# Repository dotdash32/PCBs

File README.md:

# PCBs

Printed Circuit Board Designs, primarily for keyboards.

I'm keeping all the PCB files here, including works in progress and ones that aren't labelled super well.  
Not everything is tested, but everything should be mostly ok.

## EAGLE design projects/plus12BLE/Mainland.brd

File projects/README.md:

# Projects

All my projects in EAGLE, even some outdated/inactive ones.

## Active Projects

* plus12 (upcoming GB as of summer 2018)

* Handwire Support

Other projects are outdated/inactive.  I'm keeping these here in case anyone wants a CamelDox.

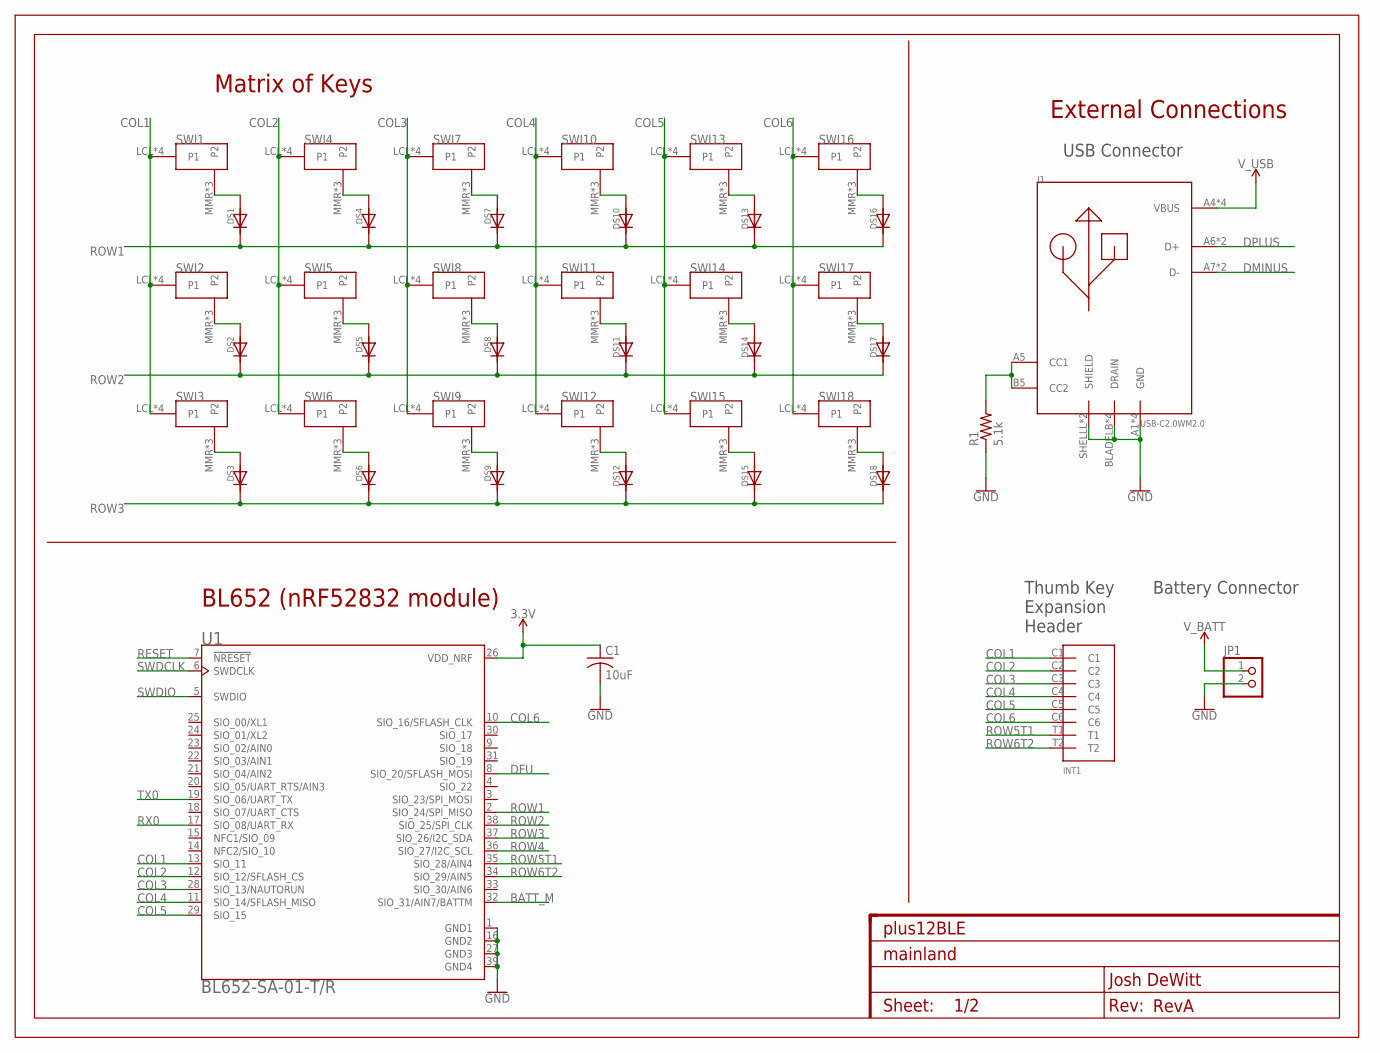
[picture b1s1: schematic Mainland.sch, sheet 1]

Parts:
C1: 10uF; C0805K
DS1, DS2, DS3, DS4, DS5, DS6, DS7, DS8, DS9, DS10, DS11, DS12, DS13, DS14, DS15, DS16, DS17, DS18: DIODECOMBO; DIODE_COMBO
FRAME1: FRAME_LTR_CU_MARK; FR-LTR-ON-PCB
INT1: INTRCNNT4X2; INTRRIBBON
J1: USB-C2.0WM2.0; WM17904_SIMP
JP1: PINHD-1X2; 1X02
R1: 5.1k; R0603
SWI1, SWI2, SWI3, SWI4, SWI5, SWI6, SWI7, SWI8, SWI9, SWI10, SWI11, SWI12, SWI13, SWI14, SWI15, SWI16, SWI17, SWI18: MX/ALPSDOUBLE_SLOT; DOUBLED_SLOTS
U1: BL652-SA-01-T/R; XCVR_BL652-SA-01-T/R

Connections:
3.3V: C1.1, U1.26 (VDD_NRF); also elsewhere on the board
BATT_M: U1.32 (SIO_31/AIN7/BATTM); also elsewhere on the board
COL1: INT1.C1, SWI1.LCL (P1), SWI1.LLP (P1), SWI1.LRLP (P1), SWI1.MML (P1), SWI2.LCL (P1), SWI2.LLP (P1), SWI2.LRLP (P1), SWI2.MML (P1), SWI3.LCL (P1), SWI3.LLP (P1), SWI3.LRLP (P1), SWI3.MML (P1), U1.13 (SIO_11)
COL2: INT1.C2, SWI4.LCL (P1), SWI4.LLP (P1), SWI4.LRLP (P1), SWI4.MML (P1), SWI5.LCL (P1), SWI5.LLP (P1), SWI5.LRLP (P1), SWI5.MML (P1), SWI6.LCL (P1), SWI6.LLP (P1), SWI6.LRLP (P1), SWI6.MML (P1), U1.12 (SIO_12/SFLASH_CS)
COL3: INT1.C3, SWI7.LCL (P1), SWI7.LLP (P1), SWI7.LRLP (P1), SWI7.MML (P1), SWI8.LCL (P1), SWI8.LLP (P1), SWI8.LRLP (P1), SWI8.MML (P1), SWI9.LCL (P1), SWI9.LLP (P1), SWI9.LRLP (P1), SWI9.MML (P1), U1.28 (SIO_13/NAUTORUN)
COL4: INT1.C4, SWI10.LCL (P1), SWI10.LLP (P1), SWI10.LRLP (P1), SWI10.MML (P1), SWI11.LCL (P1), SWI11.LLP (P1), SWI11.LRLP (P1), SWI11.MML (P1), SWI12.LCL (P1), SWI12.LLP (P1), SWI12.LRLP (P1), SWI12.MML (P1), U1.11 (SIO_14/SFLASH_MISO)
COL5: INT1.C5, SWI13.LCL (P1), SWI13.LLP (P1), SWI13.LRLP (P1), SWI13.MML (P1), SWI14.LCL (P1), SWI14.LLP (P1), SWI14.LRLP (P1), SWI14.MML (P1), SWI15.LCL (P1), SWI15.LLP (P1), SWI15.LRLP (P1), SWI15.MML (P1), U1.29 (SIO_15)
COL6: INT1.C6, SWI16.LCL (P1), SWI16.LLP (P1), SWI16.LRLP (P1), SWI16.MML (P1), SWI17.LCL (P1), SWI17.LLP (P1), SWI17.LRLP (P1), SWI17.MML (P1), SWI18.LCL (P1), SWI18.LLP (P1), SWI18.LRLP (P1), SWI18.MML (P1), U1.10 (SIO_16/SFLASH_CLK)
DFU: U1.8 (SIO_20/SFLASH_MOSI); also elsewhere on the board
DMINUS: J1.A7 (D-), J1.B7 (D-); also elsewhere on the board
DPLUS: J1.A6 (D+), J1.B6 (D+); also elsewhere on the board
GND: C1.2, J1.A1 (GND), J1.A12 (GND), J1.B1 (GND), J1.B12 (GND), J1.BLADELB (DRAIN), J1.BLADELF (DRAIN), J1.BLADERB (DRAIN), J1.BLADERF (DRAIN), J1.SHELLL (SHIELD), J1.SHELLR (SHIELD), JP1.2, R1.1, U1.1 (GND1), U1.16 (GND2), U1.27 (GND3), U1.39 (GND4); also elsewhere on the board
unnamed: DS1.ANOST (AN), DS1.ANOT (AN), SWI1.MMR (P2), SWI1.RCL (P2), SWI1.RLMID (P2)
unnamed: DS4.ANOST (AN), DS4.ANOT (AN), SWI4.MMR (P2), SWI4.RCL (P2), SWI4.RLMID (P2)
unnamed: DS7.ANOST (AN), DS7.ANOT (AN), SWI7.MMR (P2), SWI7.RCL (P2), SWI7.RLMID (P2)
unnamed: DS10.ANOST (AN), DS10.ANOT (AN), SWI10.MMR (P2), SWI10.RCL (P2), SWI10.RLMID (P2)
unnamed: DS13.ANOST (AN), DS13.ANOT (AN), SWI13.MMR (P2), SWI13.RCL (P2), SWI13.RLMID (P2)
unnamed: DS16.ANOST (AN), DS16.ANOT (AN), SWI16.MMR (P2), SWI16.RCL (P2), SWI16.RLMID (P2)
unnamed: DS2.ANOST (AN), DS2.ANOT (AN), SWI2.MMR (P2), SWI2.RCL (P2), SWI2.RLMID (P2)
unnamed: DS5.ANOST (AN), DS5.ANOT (AN), SWI5.MMR (P2), SWI5.RCL (P2), SWI5.RLMID (P2)
unnamed: DS8.ANOST (AN), DS8.ANOT (AN), SWI8.MMR (P2), SWI8.RCL (P2), SWI8.RLMID (P2)
unnamed: DS11.ANOST (AN), DS11.ANOT (AN), SWI11.MMR (P2), SWI11.RCL (P2), SWI11.RLMID (P2)
unnamed: DS14.ANOST (AN), DS14.ANOT (AN), SWI14.MMR (P2), SWI14.RCL (P2), SWI14.RLMID (P2)
unnamed: DS17.ANOST (AN), DS17.ANOT (AN), SWI17.MMR (P2), SWI17.RCL (P2), SWI17.RLMID (P2)
unnamed: DS3.ANOST (AN), DS3.ANOT (AN), SWI3.MMR (P2), SWI3.RCL (P2), SWI3.RLMID (P2)
unnamed: DS6.ANOST (AN), DS6.ANOT (AN), SWI6.MMR (P2), SWI6.RCL (P2), SWI6.RLMID (P2)
unnamed: DS9.ANOST (AN), DS9.ANOT (AN), SWI9.MMR (P2), SWI9.RCL (P2), SWI9.RLMID (P2)
unnamed: DS12.ANOST (AN), DS12.ANOT (AN), SWI12.MMR (P2), SWI12.RCL (P2), SWI12.RLMID (P2)
unnamed: DS15.ANOST (AN), DS15.ANOT (AN), SWI15.MMR (P2), SWI15.RCL (P2), SWI15.RLMID (P2)
unnamed: DS18.ANOST (AN), DS18.ANOT (AN), SWI18.MMR (P2), SWI18.RCL (P2), SWI18.RLMID (P2)
unnamed: J1.A5 (CC1), J1.B5 (CC2), R1.2
RESET: U1.7 (!NRESET); also elsewhere on the board
ROW1: DS1.CATST (CAT), DS1.CATT (CAT), DS4.CATST (CAT), DS4.CATT (CAT), DS7.CATST (CAT), DS7.CATT (CAT), DS10.CATST (CAT), DS10.CATT (CAT), DS13.CATST (CAT), DS13.CATT (CAT), DS16.CATST (CAT), DS16.CATT (CAT), U1.2 (SIO_24/SPI_MISO)
ROW2: DS2.CATST (CAT), DS2.CATT (CAT), DS5.CATST (CAT), DS5.CATT (CAT), DS8.CATST (CAT), DS8.CATT (CAT), DS11.CATST (CAT), DS11.CATT (CAT), DS14.CATST (CAT), DS14.CATT (CAT), DS17.CATST (CAT), DS17.CATT (CAT), U1.38 (SIO_25/SPI_CLK)
ROW3: DS3.CATST (CAT), DS3.CATT (CAT), DS6.CATST (CAT), DS6.CATT (CAT), DS9.CATST (CAT), DS9.CATT (CAT), DS12.CATST (CAT), DS12.CATT (CAT), DS15.CATST (CAT), DS15.CATT (CAT), DS18.CATST (CAT), DS18.CATT (CAT), U1.37 (SIO_26/I2C_SDA)
ROW4: U1.36 (SIO_27/I2C_SCL)
ROW5T1: INT1.T1, U1.35 (SIO_28/AIN4)
ROW6T2: INT1.T2, U1.34 (SIO_29/AIN5)
RX0: U1.17 (SIO_08/UART_RX); also elsewhere on the board
SWDCLK: U1.6 (SWDCLK); also elsewhere on the board
SWDIO: U1.5 (SWDIO); also elsewhere on the board
TX0: U1.19 (SIO_06/UART_TX); also elsewhere on the board
V_BATT: JP1.1; also elsewhere on the board
V_USB: J1.A4 (VBUS), J1.A9 (VBUS), J1.B4 (VBUS), J1.B9 (VBUS); also elsewhere on the board

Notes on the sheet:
Matrix of Keys
External Connections
USB Connector
Battery Connector
Thumb Key Expansion Header
BL652 (nRF52832 module)

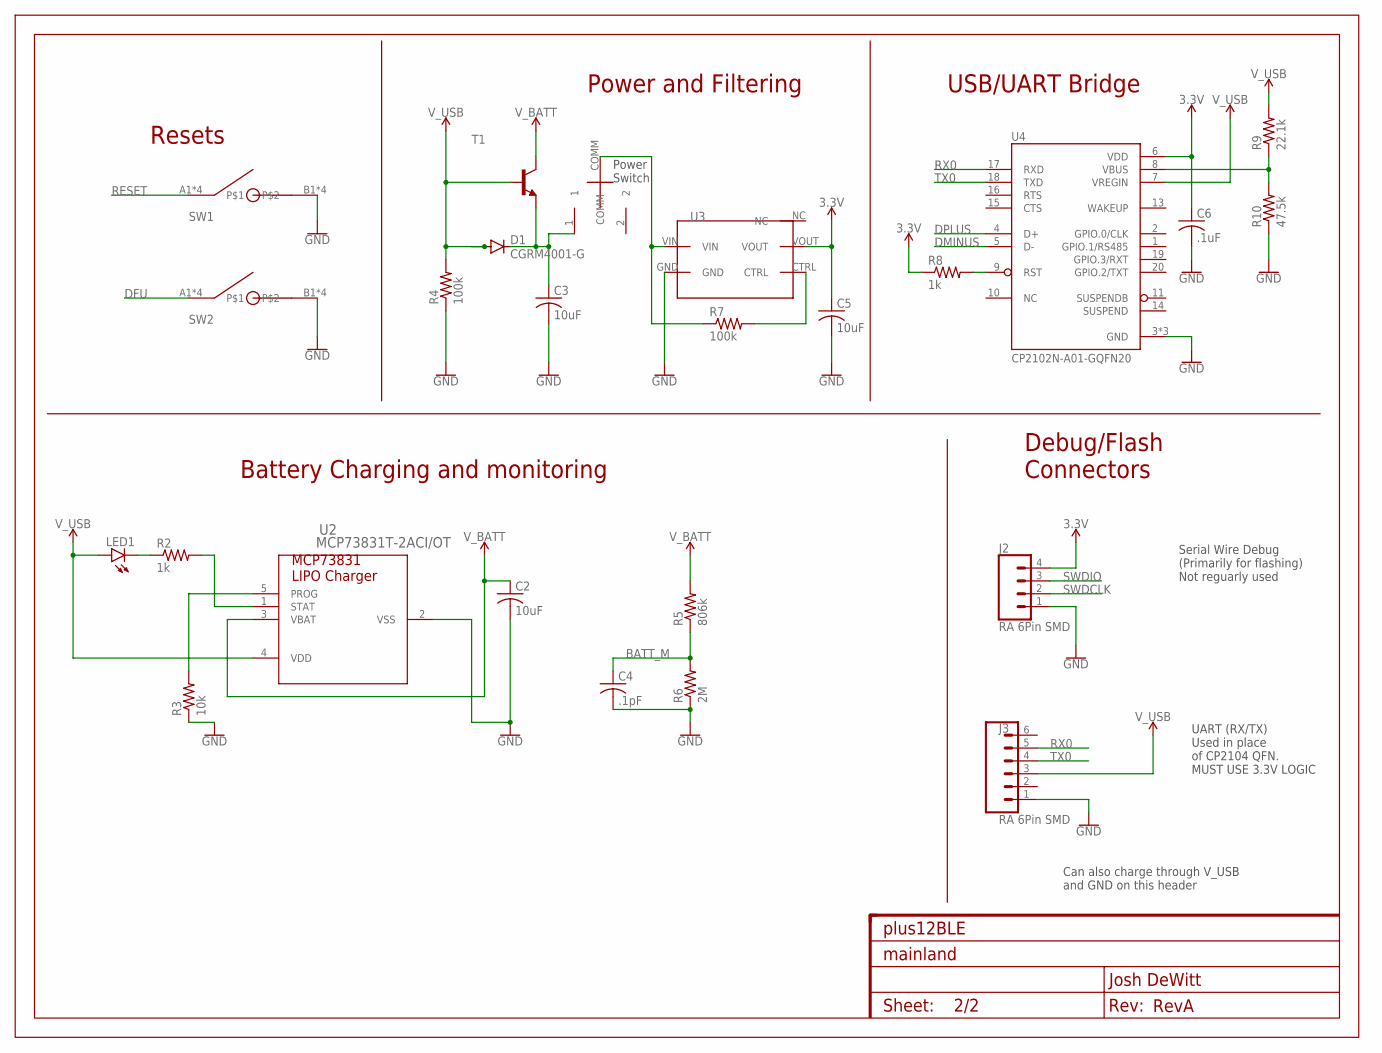
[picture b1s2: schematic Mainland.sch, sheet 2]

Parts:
C2, C3, C5: 10uF; C0805K
C4: .1pF; C0603
C6: .1uF; C0603
D1: CGRM4001-G; SOD-123_MINI-SMA
FRAME2: FRAME_LTR_CU_MARK; FR-LTR-ON-PCB
J2: RA 6Pin SMD; 1X04_SMD_RA_FEMALE
J3: RA 6Pin SMD; 1X06-SMD_RA_MALE
LED1: LEDCHIP-LED0603; CHIP-LED0603
R2, R8: 1k; R0603
R3: 10k; R0603
R4, R7: 100k; R0603
R5: 806k; R0603
R6: 2M; R0603
R9: 22.1k; R0603
R10: 47.5k; R0603
SW1, SW2: RSTSWSMALL_SMD; EVP-BBA
SW3: SLIDER_SWITCH; MHSS1105
T1: BC808-NPN-SOT23-BEC; SOT23-BEC
U2: MCP73831T-2ACI/OT; SOT-23-5_MC
U3: TCR2EF
U4: CP2102N-A01-GQFN20; SILABS_QFN20

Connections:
3.3V: C5.1, C6.1, J2.4, R8.1, U3.VOUT, U4.6 (VDD); also elsewhere on the board
BATT_M: C4.1, R5.1, R6.2; also elsewhere on the board
DFU: SW2.A1, SW2.A2, SW2.A3, SW2.A4; also elsewhere on the board
DMINUS: U4.5 (D-); also elsewhere on the board
DPLUS: U4.4 (D+); also elsewhere on the board
GND: C2.2, C3.2, C4.2, C5.2, C6.2, J2.1, J3.1, R3.1, R4.1, R6.1, R10.1, SW1.B1, SW1.B2, SW1.B3, SW1.B4, SW2.B1, SW2.B2, SW2.B3, SW2.B4, U2.2 (VSS), U3.GND, U4.3 (GND), U4.12 (GND), U4.21 (GND); also elsewhere on the board
unnamed: R7.2, U3.CTRL
unnamed: R7.1, SW3.COMM, U3.VIN
unnamed: LED1.C, R2.1
unnamed: R2.2, U2.1 (STAT)
unnamed: R3.2, U2.5 (PROG)
unnamed: R9.1, R10.2, U4.8 (VBUS)
unnamed: R8.2, U4.9 (RST)
unnamed: C3.1, D1.C, SW3.1, T1.E
RESET: SW1.A1, SW1.A2, SW1.A3, SW1.A4; also elsewhere on the board
RX0: J3.5, U4.17 (RXD); also elsewhere on the board
SWDCLK: J2.2; also elsewhere on the board
SWDIO: J2.3; also elsewhere on the board
TX0: J3.4, U4.18 (TXD); also elsewhere on the board
V_BATT: C2.1, R5.2, T1.C, U2.3 (VBAT); also elsewhere on the board
V_USB: D1.A, J3.3, LED1.A, R4.2, R9.2, T1.B, U2.4 (VDD), U4.7 (VREGIN); also elsewhere on the board

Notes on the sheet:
Resets
Power and Filtering
Battery Charging and monitoring
USB/UART Bridge
Debug/Flash Connectors
Serial Wire Debug (Primarily for flashing) Not reguarly used
UART (RX/TX) Used in place of CP2104 QFN. MUST USE 3.3V LOGIC
Can also charge through V_USB and GND on this header
Power Switch

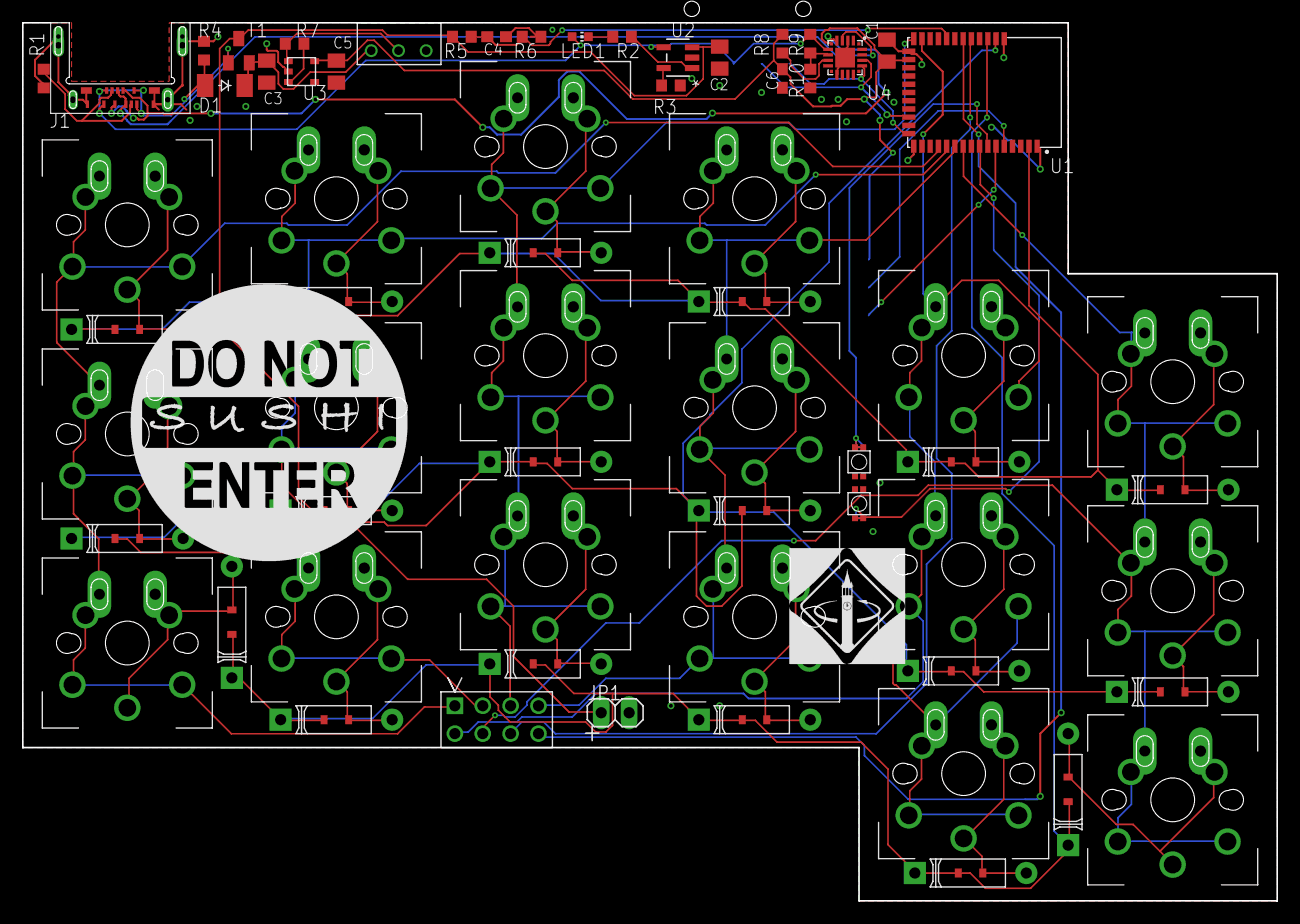
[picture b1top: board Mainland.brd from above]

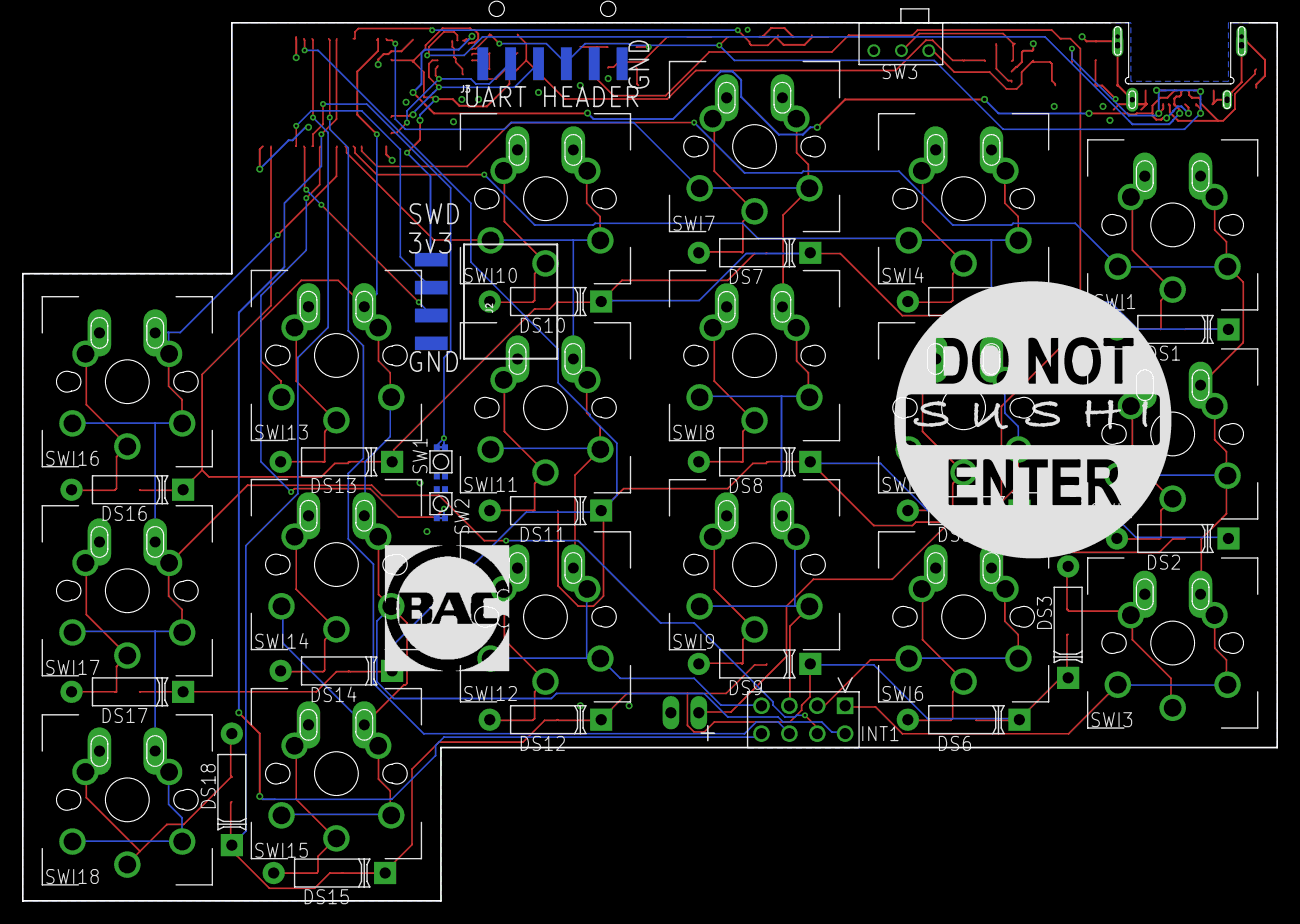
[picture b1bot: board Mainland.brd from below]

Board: 2 copper layers, 114.3 x 80.0 mm, 73 parts (4 on the bottom side), 51 nets.

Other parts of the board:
U$1, U$3: 1INCH_TOP
U$2: BAC_SELLOUT
U$4: IEEE_BERKELEY

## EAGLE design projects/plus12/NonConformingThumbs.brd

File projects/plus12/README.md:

# Plus 12

A split keyboard with a bunch of different options.
There are 2 basic main matrix options, either 5 or 6 columns.
There are 3 main thumb configurations:
a full circuluar curve, adjustable down to 3 keys,
a circular curve into a straight row at key four, adjustable down to 5 keys (4 and fewer is the same as the full circle),
a straight row of keys, adjustable down to 3 keys.
There is potential for a 4x2 grid (like a Mitosis board) in the works as well.

[Current Geekhack](https://geekhack.org/index.php?topic=96658.0) and [Reddit](https://www.reddit.com/r/MechanicalKeyboards/comments/8zpj9u/ic_plus12_split_ergonomic_keyboard/) interest check threads.

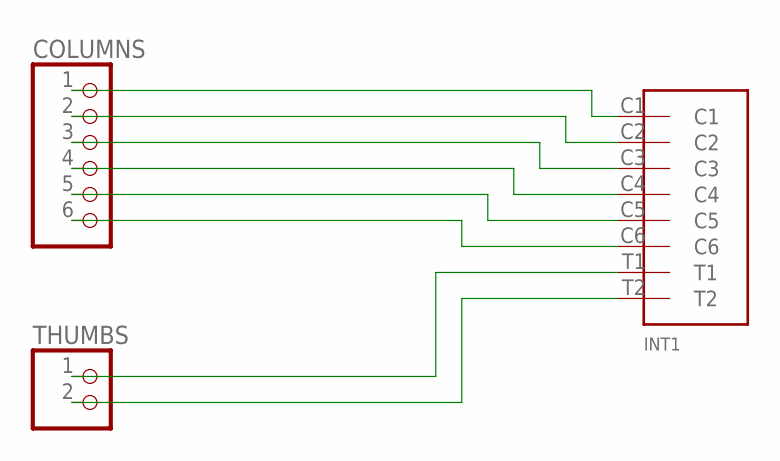
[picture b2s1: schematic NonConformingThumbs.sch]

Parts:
COLUMNS: PINHD-1X6; 1X06
INT1: INTRCNNT4X2; INTRRIBBON
THUMBS: PINHD-1X2; 1X02

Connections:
unnamed: COLUMNS.1, INT1.C1
unnamed: COLUMNS.2, INT1.C2
unnamed: COLUMNS.3, INT1.C3
unnamed: COLUMNS.4, INT1.C4
unnamed: COLUMNS.5, INT1.C5
unnamed: COLUMNS.6, INT1.C6
unnamed: INT1.T1, THUMBS.1
unnamed: INT1.T2, THUMBS.2

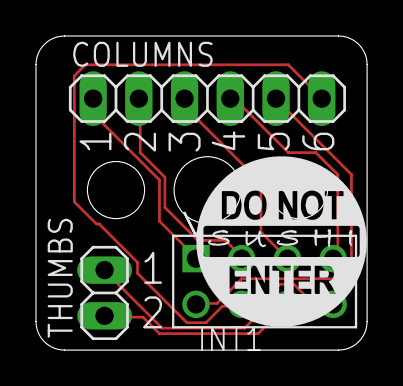
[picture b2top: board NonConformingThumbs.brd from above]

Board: 2 copper layers, 18.4 x 17.4 mm, 4 parts (0 on the bottom side), 8 nets.

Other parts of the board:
U$1: 3_8INCH_TOP

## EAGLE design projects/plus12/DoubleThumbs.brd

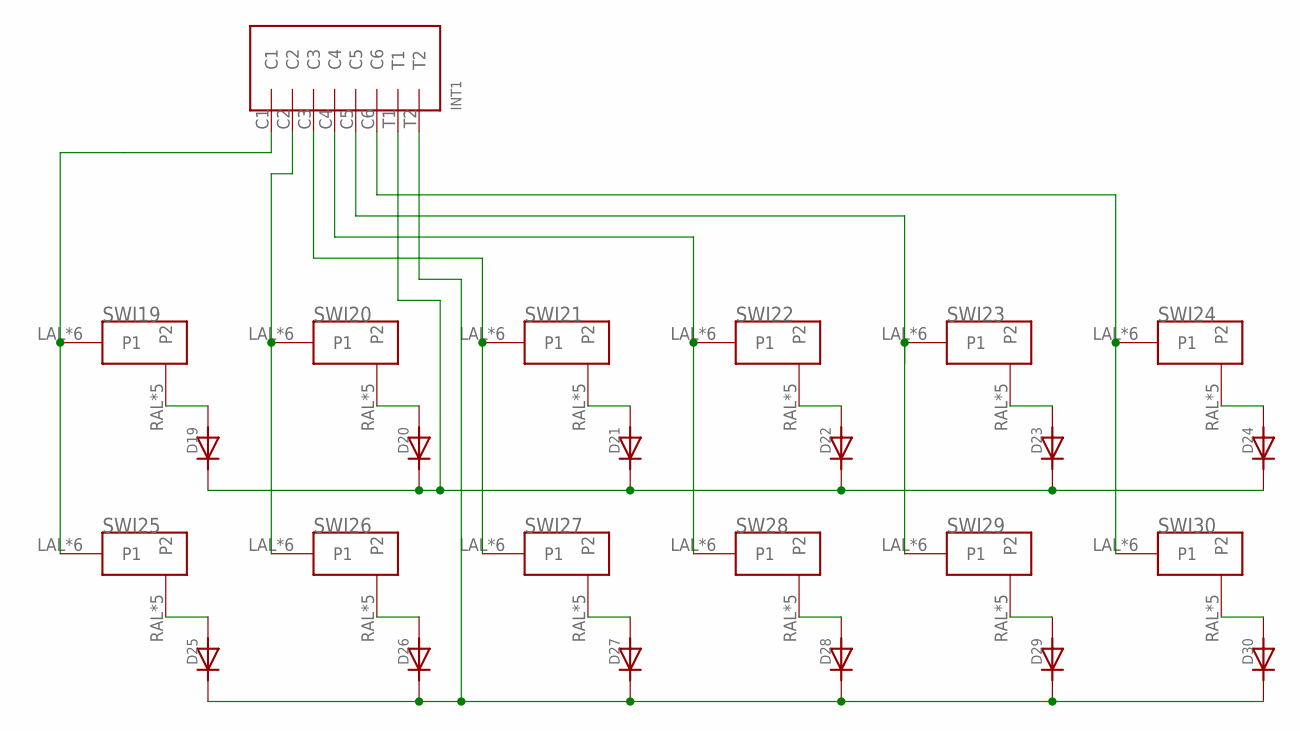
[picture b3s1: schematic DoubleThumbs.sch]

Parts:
D19, D20, D21, D22, D23, D24, D25, D26, D27, D28, D29, D30: DIODE; DIODE_COMBO
INT1: INTRCNNT4X2; INTRRIBBON
SW28: MX/ALPSDOUBLESIDED; DOUBLED_MX/ALPS
SWI19, SWI20, SWI21, SWI22, SWI23, SWI24, SWI25, SWI26, SWI27, SWI29, SWI30: MX/ALPSDOUBLESIDED; DOUBLED_MX/ALPS

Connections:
unnamed: D19.ANOSB (AN), D19.ANOST (AN), D19.ANOT (AN), SWI19.RAL (P2), SWI19.RAR (P2), SWI19.RCL (P2), SWI19.RCR (P2), SWI19.RLMID (P2)
unnamed: D20.ANOSB (AN), D20.ANOST (AN), D20.ANOT (AN), SWI20.RAL (P2), SWI20.RAR (P2), SWI20.RCL (P2), SWI20.RCR (P2), SWI20.RLMID (P2)
unnamed: D21.ANOSB (AN), D21.ANOST (AN), D21.ANOT (AN), SWI21.RAL (P2), SWI21.RAR (P2), SWI21.RCL (P2), SWI21.RCR (P2), SWI21.RLMID (P2)
unnamed: D22.ANOSB (AN), D22.ANOST (AN), D22.ANOT (AN), SWI22.RAL (P2), SWI22.RAR (P2), SWI22.RCL (P2), SWI22.RCR (P2), SWI22.RLMID (P2)
unnamed: D23.ANOSB (AN), D23.ANOST (AN), D23.ANOT (AN), SWI23.RAL (P2), SWI23.RAR (P2), SWI23.RCL (P2), SWI23.RCR (P2), SWI23.RLMID (P2)
unnamed: D24.ANOSB (AN), D24.ANOST (AN), D24.ANOT (AN), SWI24.RAL (P2), SWI24.RAR (P2), SWI24.RCL (P2), SWI24.RCR (P2), SWI24.RLMID (P2)
unnamed: D25.ANOSB (AN), D25.ANOST (AN), D25.ANOT (AN), SWI25.RAL (P2), SWI25.RAR (P2), SWI25.RCL (P2), SWI25.RCR (P2), SWI25.RLMID (P2)
unnamed: D26.ANOSB (AN), D26.ANOST (AN), D26.ANOT (AN), SWI26.RAL (P2), SWI26.RAR (P2), SWI26.RCL (P2), SWI26.RCR (P2), SWI26.RLMID (P2)
unnamed: D27.ANOSB (AN), D27.ANOST (AN), D27.ANOT (AN), SWI27.RAL (P2), SWI27.RAR (P2), SWI27.RCL (P2), SWI27.RCR (P2), SWI27.RLMID (P2)
unnamed: D28.ANOSB (AN), D28.ANOST (AN), D28.ANOT (AN), SW28.RAL (P2), SW28.RAR (P2), SW28.RCL (P2), SW28.RCR (P2), SW28.RLMID (P2)
unnamed: D29.ANOSB (AN), D29.ANOST (AN), D29.ANOT (AN), SWI29.RAL (P2), SWI29.RAR (P2), SWI29.RCL (P2), SWI29.RCR (P2), SWI29.RLMID (P2)
unnamed: D30.ANOSB (AN), D30.ANOST (AN), D30.ANOT (AN), SWI30.RAL (P2), SWI30.RAR (P2), SWI30.RCL (P2), SWI30.RCR (P2), SWI30.RLMID (P2)
unnamed: D25.CATSB (CAT), D25.CATST (CAT), D25.CATT (CAT), D26.CATSB (CAT), D26.CATST (CAT), D26.CATT (CAT), D27.CATSB (CAT), D27.CATST (CAT), D27.CATT (CAT), D28.CATSB (CAT), D28.CATST (CAT), D28.CATT (CAT), D29.CATSB (CAT), D29.CATST (CAT), D29.CATT (CAT), D30.CATSB (CAT), D30.CATST (CAT), D30.CATT (CAT), INT1.T2
unnamed: INT1.C1, SWI19.LAL (P1), SWI19.LAR (P1), SWI19.LCL (P1), SWI19.LCR (P1), SWI19.LLP (P1), SWI19.LRLP (P1), SWI25.LAL (P1), SWI25.LAR (P1), SWI25.LCL (P1), SWI25.LCR (P1), SWI25.LLP (P1), SWI25.LRLP (P1)
unnamed: INT1.C2, SWI20.LAL (P1), SWI20.LAR (P1), SWI20.LCL (P1), SWI20.LCR (P1), SWI20.LLP (P1), SWI20.LRLP (P1), SWI26.LAL (P1), SWI26.LAR (P1), SWI26.LCL (P1), SWI26.LCR (P1), SWI26.LLP (P1), SWI26.LRLP (P1)
unnamed: INT1.C3, SWI21.LAL (P1), SWI21.LAR (P1), SWI21.LCL (P1), SWI21.LCR (P1), SWI21.LLP (P1), SWI21.LRLP (P1), SWI27.LAL (P1), SWI27.LAR (P1), SWI27.LCL (P1), SWI27.LCR (P1), SWI27.LLP (P1), SWI27.LRLP (P1)
unnamed: INT1.C4, SW28.LAL (P1), SW28.LAR (P1), SW28.LCL (P1), SW28.LCR (P1), SW28.LLP (P1), SW28.LRLP (P1), SWI22.LAL (P1), SWI22.LAR (P1), SWI22.LCL (P1), SWI22.LCR (P1), SWI22.LLP (P1), SWI22.LRLP (P1)
unnamed: INT1.C5, SWI23.LAL (P1), SWI23.LAR (P1), SWI23.LCL (P1), SWI23.LCR (P1), SWI23.LLP (P1), SWI23.LRLP (P1), SWI29.LAL (P1), SWI29.LAR (P1), SWI29.LCL (P1), SWI29.LCR (P1), SWI29.LLP (P1), SWI29.LRLP (P1)
unnamed: INT1.C6, SWI24.LAL (P1), SWI24.LAR (P1), SWI24.LCL (P1), SWI24.LCR (P1), SWI24.LLP (P1), SWI24.LRLP (P1), SWI30.LAL (P1), SWI30.LAR (P1), SWI30.LCL (P1), SWI30.LCR (P1), SWI30.LLP (P1), SWI30.LRLP (P1)
unnamed: D19.CATSB (CAT), D19.CATST (CAT), D19.CATT (CAT), D20.CATSB (CAT), D20.CATST (CAT), D20.CATT (CAT), D21.CATSB (CAT), D21.CATST (CAT), D21.CATT (CAT), D22.CATSB (CAT), D22.CATST (CAT), D22.CATT (CAT), D23.CATSB (CAT), D23.CATST (CAT), D23.CATT (CAT), D24.CATSB (CAT), D24.CATST (CAT), D24.CATT (CAT), INT1.T1

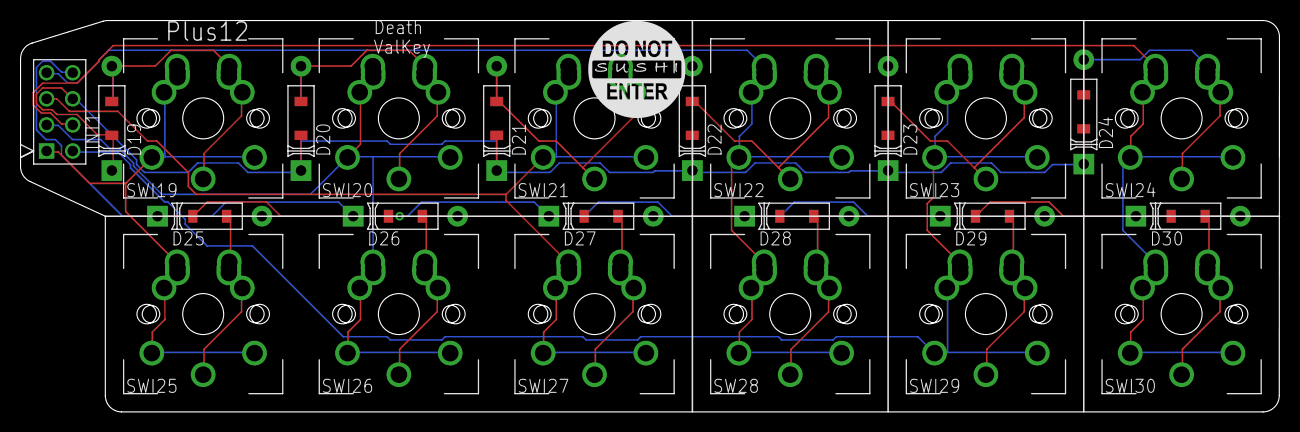
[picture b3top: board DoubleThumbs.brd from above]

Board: 2 copper layers, 122.6 x 38.1 mm, 27 parts (0 on the bottom side), 20 nets.

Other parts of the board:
U$1: 3_8INCH_BOT
U$2: 3_8INCH_TOP

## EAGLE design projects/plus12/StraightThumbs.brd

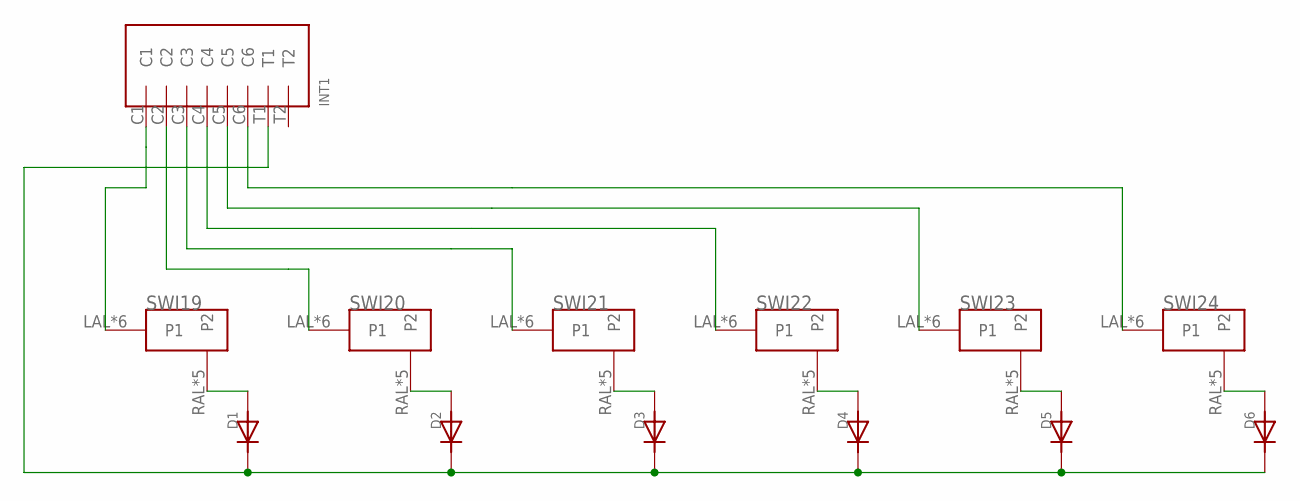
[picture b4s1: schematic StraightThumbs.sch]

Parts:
D1, D2, D3, D4, D5, D6: DIODE; DIODE_COMBO
INT1: INTRCNNT4X2; INTRRIBBON
SWI19, SWI20, SWI21, SWI22, SWI23, SWI24: MX/ALPSDOUBLESIDED; DOUBLED_MX/ALPS

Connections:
unnamed: D1.ANOSB (AN), D1.ANOST (AN), D1.ANOT (AN), SWI19.RAL (P2), SWI19.RAR (P2), SWI19.RCL (P2), SWI19.RCR (P2), SWI19.RLMID (P2)
unnamed: D2.ANOSB (AN), D2.ANOST (AN), D2.ANOT (AN), SWI20.RAL (P2), SWI20.RAR (P2), SWI20.RCL (P2), SWI20.RCR (P2), SWI20.RLMID (P2)
unnamed: D3.ANOSB (AN), D3.ANOST (AN), D3.ANOT (AN), SWI21.RAL (P2), SWI21.RAR (P2), SWI21.RCL (P2), SWI21.RCR (P2), SWI21.RLMID (P2)
unnamed: D4.ANOSB (AN), D4.ANOST (AN), D4.ANOT (AN), SWI22.RAL (P2), SWI22.RAR (P2), SWI22.RCL (P2), SWI22.RCR (P2), SWI22.RLMID (P2)
unnamed: D5.ANOSB (AN), D5.ANOST (AN), D5.ANOT (AN), SWI23.RAL (P2), SWI23.RAR (P2), SWI23.RCL (P2), SWI23.RCR (P2), SWI23.RLMID (P2)
unnamed: D6.ANOSB (AN), D6.ANOST (AN), D6.ANOT (AN), SWI24.RAL (P2), SWI24.RAR (P2), SWI24.RCL (P2), SWI24.RCR (P2), SWI24.RLMID (P2)
unnamed: INT1.C1, SWI19.LAL (P1), SWI19.LAR (P1), SWI19.LCL (P1), SWI19.LCR (P1), SWI19.LLP (P1), SWI19.LRLP (P1)
unnamed: INT1.C2, SWI20.LAL (P1), SWI20.LAR (P1), SWI20.LCL (P1), SWI20.LCR (P1), SWI20.LLP (P1), SWI20.LRLP (P1)
unnamed: INT1.C3, SWI21.LAL (P1), SWI21.LAR (P1), SWI21.LCL (P1), SWI21.LCR (P1), SWI21.LLP (P1), SWI21.LRLP (P1)
unnamed: INT1.C4, SWI22.LAL (P1), SWI22.LAR (P1), SWI22.LCL (P1), SWI22.LCR (P1), SWI22.LLP (P1), SWI22.LRLP (P1)
unnamed: INT1.C5, SWI23.LAL (P1), SWI23.LAR (P1), SWI23.LCL (P1), SWI23.LCR (P1), SWI23.LLP (P1), SWI23.LRLP (P1)
unnamed: INT1.C6, SWI24.LAL (P1), SWI24.LAR (P1), SWI24.LCL (P1), SWI24.LCR (P1), SWI24.LLP (P1), SWI24.LRLP (P1)
unnamed: D1.CATSB (CAT), D1.CATST (CAT), D1.CATT (CAT), D2.CATSB (CAT), D2.CATST (CAT), D2.CATT (CAT), D3.CATSB (CAT), D3.CATST (CAT), D3.CATT (CAT), D4.CATSB (CAT), D4.CATST (CAT), D4.CATT (CAT), D5.CATSB (CAT), D5.CATST (CAT), D5.CATT (CAT), D6.CATSB (CAT), D6.CATST (CAT), D6.CATT (CAT), INT1.T1

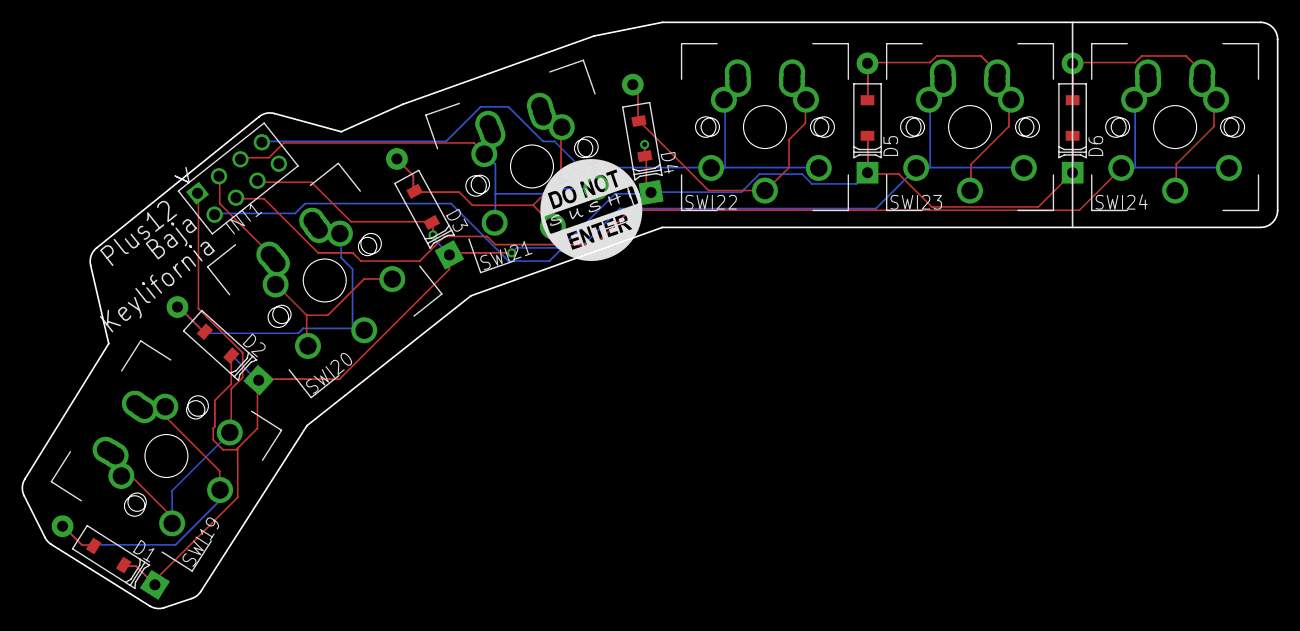
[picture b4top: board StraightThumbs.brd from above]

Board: 2 copper layers, 116.6 x 54.5 mm, 15 parts (0 on the bottom side), 13 nets.

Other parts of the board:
U$1: 3_8INCH_TOP
U$2: 3_8INCH_BOT

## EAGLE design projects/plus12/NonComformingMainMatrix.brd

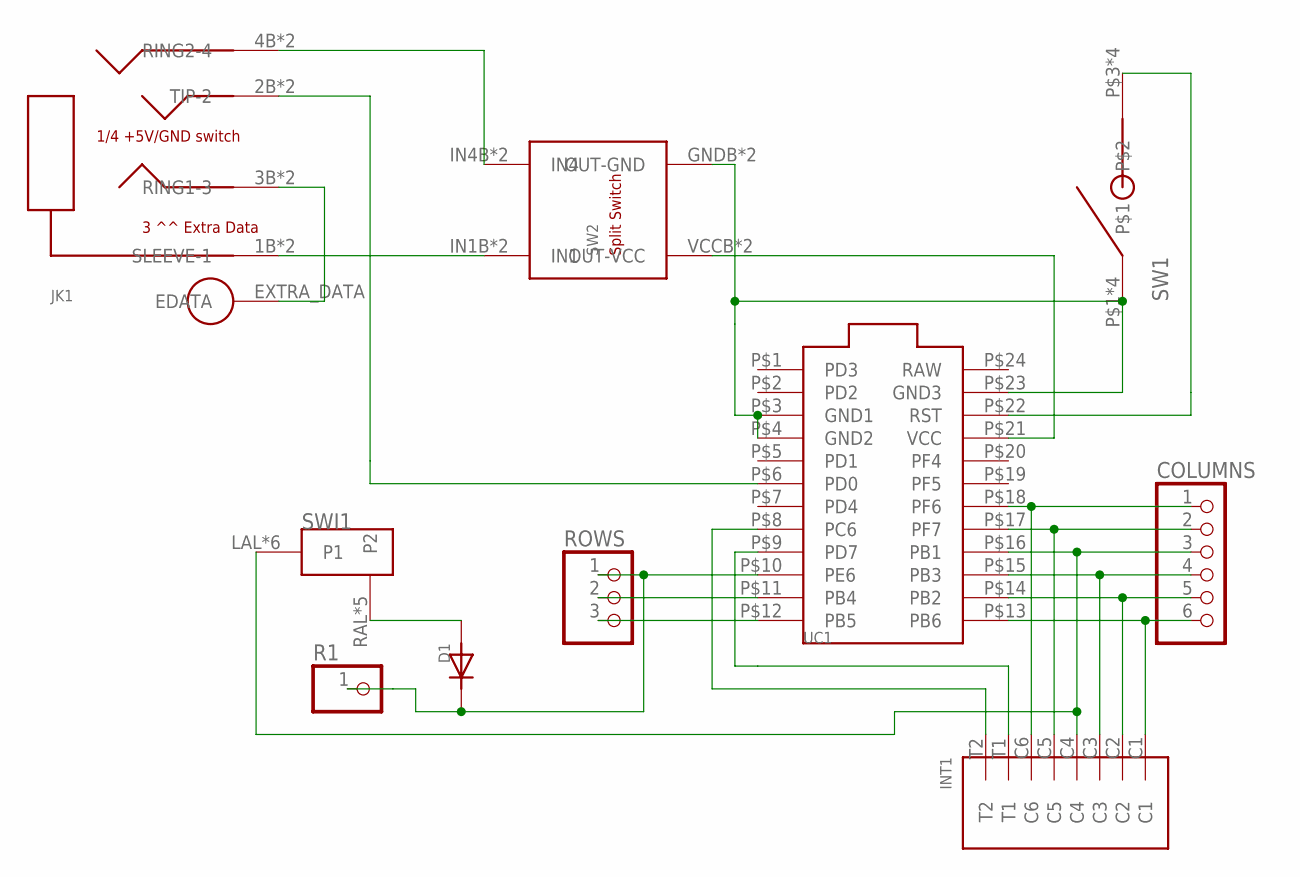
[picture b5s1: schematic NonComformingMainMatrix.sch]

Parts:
COLUMNS: PINHD-1X6; 1X06
D1: DIODE; DIODE_COMBO
INT1: INTRCNNT4X2; INTRRIBBON
JK1: TRRSJACKUNDER; TRRSJACK
R1: PINHD-1X1; 1X01
ROWS: PINHD-1X3; 1X03
SW1: RSTSWSMD; FLATSWT
SW2: TRANSFERPADDY; TRANSFER_PADS
SWI1: MX/ALPSDOUBLESIDED; DOUBLED_MX/ALPS
UC1: PROMICROUNDER; PROMICRO_UNDER

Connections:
unnamed: ROWS.3, UC1.P$12 (PB5)
unnamed: ROWS.2, UC1.P$11 (PB4)
unnamed: D1.CATSB (CAT), D1.CATST (CAT), D1.CATT (CAT), R1.1, ROWS.1, UC1.P$10 (PE6)
unnamed: INT1.T1, UC1.P$9 (PD7)
unnamed: INT1.T2, UC1.P$8 (PC6)
unnamed: COLUMNS.6, INT1.C1, UC1.P$13 (PB6)
unnamed: COLUMNS.5, INT1.C2, UC1.P$14 (PB2)
unnamed: COLUMNS.4, INT1.C3, UC1.P$15 (PB3)
unnamed: COLUMNS.3, INT1.C4, SWI1.LAL (P1), SWI1.LAR (P1), SWI1.LCL (P1), SWI1.LCR (P1), SWI1.LLP (P1), SWI1.LRLP (P1), UC1.P$16 (PB1)
unnamed: COLUMNS.2, INT1.C5, UC1.P$17 (PF7)
unnamed: COLUMNS.1, INT1.C6, UC1.P$18 (PF6)
unnamed: SW1.P$1, SW1.P$2, SW1.P$5, SW1.P$6, SW2.GNDB (OUT-GND), SW2.GNDT (OUT-GND), UC1.P$3 (GND1), UC1.P$4 (GND2), UC1.P$23 (GND3)
unnamed: SW1.P$3, SW1.P$4, SW1.P$7, SW1.P$8, UC1.P$22 (RST)
unnamed: D1.ANOSB (AN), D1.ANOST (AN), D1.ANOT (AN), SWI1.RAL (P2), SWI1.RAR (P2), SWI1.RCL (P2), SWI1.RCR (P2), SWI1.RLMID (P2)
unnamed: SW2.VCCB (OUT-VCC), SW2.VCCT (OUT-VCC), UC1.P$21 (VCC)
unnamed: JK1.4B (RING2-4), JK1.4T (RING2-4), SW2.IN4B (IN4), SW2.IN4T (IN4)
unnamed: JK1.1B (SLEEVE-1), JK1.1T (SLEEVE-1), SW2.IN1B (IN1), SW2.IN1T (IN1)
unnamed: JK1.3B (RING1-3), JK1.3T (RING1-3), JK1.EXTRA_DATA (EDATA)
unnamed: JK1.2B (TIP-2), JK1.2T (TIP-2), UC1.P$6 (PD0)

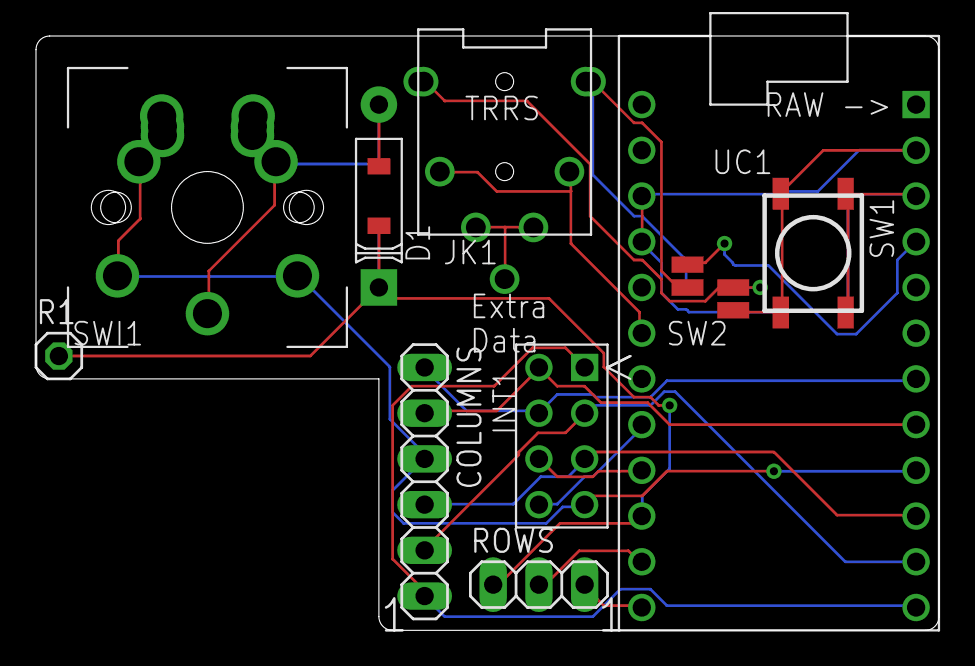
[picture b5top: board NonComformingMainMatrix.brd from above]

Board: 2 copper layers, 50.2 x 33.0 mm, 10 parts (0 on the bottom side), 19 nets.

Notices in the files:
parts and their libraries:
SparkFun-Connectors: Licensing: Creative Commons ShareAlike 4.0 International - https://creativecommons.org/licenses/by-sa/4.0
